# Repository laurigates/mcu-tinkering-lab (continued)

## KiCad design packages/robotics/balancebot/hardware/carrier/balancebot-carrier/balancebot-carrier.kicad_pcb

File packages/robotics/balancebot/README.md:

# Balancebot

Two-wheel self-balancing robot on a **Seeed XIAO RP2350**: an MPU6050 IMU
feeds a 500 Hz complementary filter and either a PID cascade or an LQR
(switchable live) on core 1, and RP2350
PIO state machines generate jitter-free step pulses for two DRV8825-driven
NEMA17 steppers. Tuning happens live over a USB CDC serial CLI; tuned
gains persist to flash.

The repo's first non-ESP32 project — built with the Raspberry Pi Pico SDK
(pinned 2.2.0) inside a container.

Design docs: [PRD-012](../../../docs/requirements/PRD-012-balancebot.md) ·
[ADR-018](../../../docs/decisions/ADR-018-pico-sdk-balancebot.md) ·
[ADR-026](../../../docs/decisions/ADR-026-balancebot-lqr-live-switch.md) ·
[WIRING.md](WIRING.md) ·
[BRINGUP.md](BRINGUP.md) (buck, straps and Vref before the first `arm`)

The project's story, at five levels of technical depth, is on
[GitHub Pages](https://laurigates.github.io/mcu-tinkering-lab/balancebot/)
([source](../../../docs/site/balancebot/index.html)).

A carrier PCB replaces the hand-wired harness: see
[`hardware/carrier/README.md`](hardware/carrier/README.md) for what is on it,
how it is generated from `hardware.toml`, and how to order it.

## Printable build guide

[`docs/build-guide.typ`](docs/build-guide.typ) → [PDF](docs/build-guide.pdf):
the whole build at the bench — bill of materials, wiring reference, power,
assembly, Vref, flashing, first boot and calibration, functional checkout,
tuning, troubleshooting.

Regenerate it after editing — GPIO numbers come from `src/pin_config.h` via
`docs/auto/pin_defs.typ`, so a pin moved in the header changes what it prints:

```bash
just balancebot::build-guide
```

The recipe pins the Typst version and the two determinism flags that
`.github/workflows/build-guide-check.yml` recompiles with, so a hand-run
`typst compile` with different flags will read as drift in CI.

## Build

```bash
# From the repo root (containerized; no local toolchain needed)
just balancebot::build          # → build/balancebot.uf2

# Host-side unit tests (PID, filter, CRC, LQR, param record; no hardware)
just balancebot::test
```

## Flash

```bash
just balancebot::flash          # picotool (reboots the board itself)
just balancebot::flash-uf2      # or: BOOTSEL drag-and-drop instructions
```

A running firmware reboots into BOOTSEL over USB, so the board's buttons are
needed only when it has crashed or its USB never enumerates. Disarm first:

```bash
picotool reboot -u -f                    # BOOTSEL; the RP2350 drive mounts
stty -f /dev/cu.usbmodem<N> 1200         # same, by the 1200-baud request
picotool reboot                          # back to the firmware
```

Both were checked on the robot on 2026-11-24 (fw 0.1.16).

## Tune

```bash
just balancebot::cli "mount down" save   # send commands, print the replies
just balancebot::stat           # also: arm, disarm
just balancebot::monitor        # watch output only; it sends nothing you type
```

```
help                 # command list
stat                 # firmware, state, gains, maxrate, model, calibration, angle, battery, pack, loop time
stream on 50         # CSV telemetry at 50 Hz (plot with any serial plotter)
log                  # run log: on/off, rate, last save, the run stored in flash (see "Untethered run log")
log list             # the runs kept in flash (newest six), newest first
log dump             # print the newest run as CSV (disarmed only); `log dump <n>` prints run n
set kp 30            # live PID gain changes
set l_eff_m 0.14     # LQR model/weight change: re-solves K, prints K, rho, residual
ctrl lqr             # switch to LQR live (bumpless); `ctrl pid` switches back
mount down           # GY-521 fitted component side down (disarmed only); `mount up` is the default
trim capture         # hold still at the balance point 2 s: sets the pitch trim (see "Pitch trim")
arm | disarm         # start/stop balancing (or hold upright 3 s to auto-arm)
drive 0.2            # while balancing: 0.2 m/s forward for 2 s, then ramps to a stop
drive 0.2 0.05 5     # ... plus 0.05 m/s turn (left wheel +, right -; > 0 = clockwise), 5 s
drive 0 0.1          # spin in place; `drive stop` ramps speed and turn to 0
rate l 800           # open-loop motor bench test (disarmed only)
cal                  # gyro bias calibration (keep the robot still); reports ok or moved
save                 # persist gains to flash (survives power cycle)
load                 # reload the saved params, gains and mount from flash (disarmed only)
set pack_r_kohm 22   # carrier divider R3: 27 (delivered boards, the default) or 22 (rev3); then `save`
set pack_cells 4     # cell count the pack warning and cutoff scale with (default 3)
```

`arm`, `mount`, `load`, `rate` and `cal` judge the state after the commands
typed before them have reached core 1 (a pasted `disarm` first is waited for, a
few control ticks at most), and refuse rather than print `OK` when core 1 would ignore them:

- `arm` in FAULT: `ERR: state FAULT — 'disarm' to clear it, or hold upright …`.
  If the IMU is not responding, holding upright cannot clear the FAULT, so the
  refusal offers only `disarm`.
- `arm` that core 1 takes but faults on in the same tick, because the robot
  lies past the 30° tilt cutoff or the IMU does not read:
  `ERR: armed, then FAULT (pitch … deg, tilt cutoff … deg) — …` or
  `ERR: armed, then FAULT — IMU not responding; …` instead of `OK`.
- `mount` and `load` while armed: `ERR: disarm first …`. Core 1 keeps the
  mount while armed. If the hold-upright gesture arms it before a `mount` (or
  the mount in `load`) arrives, the CLI says the mount stays where it was and
  `get` shows the mount core 1 applies. `load` says whether a stored record
  was found either way; when the mount was not confirmed, the parameters,
  gains and controller were still applied.
- `rate` and `cal` outside IDLE: `ERR: state RUN — 'disarm' first; …`. Core 1
  runs them only disarmed.
- Any of them while core 1 is still busy with earlier commands (a `save`
  stalls it ~45 ms): `ERR: core 1 busy …`; nothing is sent, so repeat it.

CSV columns: `t_ms,state,angle_deg,gyro_dps,setpoint_deg,rate_sps,loop_us,ctrl,pos_m,pack_v`
(`ctrl` 0 = PID, 1 = LQR; `pos_m` = commanded wheel travel since arming;
`pack_v` = pack voltage in volts, `nan` with no pack on D0).
Columns are only ever appended, so plots that index by position keep working.

### Fitting `l_eff_m` from a capture

```bash
just balancebot::capture 20                         # 20 s at 100 Hz -> tmp/balancebot/capture-<time>.csv
just balancebot::fit-leff tmp/balancebot/capture-<time>.csv 0.065   # path from the repo root; wheel diameter in m
```

Arm the robot, let it balance on its own for the capture, and do not push it:
a push is a force the LQR model lacks and drags the fit. `fit-leff` fits the
model in `src/lqr.h` to the RUN rows and prints `l_eff_m` with a 1-sigma
range, R², and the angle the balance point reads (what to add to `trim`).
Stretches where a motor stalled or skipped steps break the fit too, since the
wheel speed in the CSV is the commanded one; with R² under 0.3 it says not to
trust the result. On simulated captures it is within about 11 % (1 sigma);
`tools/fit_leff.py --self-test` runs in the host test suite.

**On the rev1 robot it has not worked.** Three balancing captures on
2026-11-23 gave R² 0.13, 0.06 and below 0.3, with `l_eff_m` estimates of
0.41 and 0.97 m that the robot's geometry rules out. A well-tuned robot moves
too little to fit, and a badly tuned one spends its time at the acceleration
clamp. Its offset estimate did agree with the mean angle, which `analyze`
reports directly. Estimate `l_eff_m` from the geometry instead ("Tuning
loop"); the LQR tolerated a rough value there.

### IMU mounting

The filter expects the GY-521 component side up, X arrow forward. On the
8d18cd8d carrier (the boards from the 2026-10-23 order) the module only wires
correctly fitted component side down, hanging rearward: that turns it 180°
about the axle, so accel X and Z both read inverted while gyro Y does not.
`IMU_PITCH_SIGN` cannot correct that (a level board reads about 180°), so the
mounting is a setting:

```
mount down           # negate accel X and Z before the filter
save                 # stored in the flash record (PARAM_VERSION 3 and later)
```

Change it only while disarmed; `stat` shows the mounting core 1 applies. With
the right setting a level board reads about 0° and tilting forward reads
positive. Records saved by older firmware load as `mount up`.

### Status LEDs

The yellow user LED blinks slowly in IDLE, stays on in RUN and blinks fast
in FAULT. The XIAO's RGB LED helps you find the auto-arm window by eye. It
uses the trimmed angle, the same one the gesture uses:

| RGB | Meaning |
|---|---|
| dim blue | IDLE, more than 5° from upright |
| yellow | within 5°: getting close |
| green, brightening | inside the ±3° window; full brightness when the 3 s hold arms it |
| solid green | RUN |
| purple | auto-arm held off (after `disarm` or `trim capture`) |
| red, blinking | FAULT |
| red, solid | IMU not responding |
| cyan, pulsing | core 1 starting (IMU init, gyro calibration) |

Brightness is capped at about 16 % of full scale.

### Pitch trim

A module that sits a degree or two off parallel to the carrier, or a robot
whose centre of mass is not over the axle when the carrier is level, balances
at a pitch other than 0. The controllers, the 3 s auto-arm window (±3°) and
the tilt cutoff all work from 0, so the robot then drives to correct a lean
that is not there, and may never auto-arm. `trim` moves 0 to the balance point:

1. Disarmed, hold the robot still where it balances and run `trim capture`
   (`just balancebot::cli "trim capture" save`).
2. For 2 s it averages the pitch; the trim becomes the current trim plus that
   average, so running it again only corrects what is left.

It refuses, leaving the trim unchanged, when the robot moved during the 2 s,
when the result would pass ±10° (usually a wrong `mount`), or when the
hold-upright gesture arms the robot first (the pose already read within ±3°
for 3 s). `set trim <deg>` sets it by hand. `trim` is subtracted from every
pitch sample, so telemetry shows the trimmed angle. It is limited to ±10° and
can be changed while armed. Records saved before PARAM_VERSION 4 load with
`trim 0`.

### Gyro calibration

The gyro bias is measured at boot, over 1 s with the robot at rest. If the
gyro or accel spreads more than a still robot would in that second (3 °/s
or 0.1 g peak to peak), the window is discarded and repeated, up to five
times; after that the robot runs with the last good bias, or none. `stat`
shows the result on its `gyro cal:` line, and `cal` repeats it on demand,
reporting `OK` or that the robot moved.

### A held I2C bus

A reset in the middle of an IMU read can leave the MPU6050 holding SDA low,
and USB power keeps it in that state across a reboot. Older firmware then
hung core 1 before its loop, and `stat` showed `imu: NOT RESPONDING` with
tick 0. Now every I2C transfer is bounded to 1 ms, and a held line is
freed (up to nine SCL clocks, then a STOP) at init and after any timed-out
transfer. `stat` counts these on an `imu bus:` line. During the first few
seconds after boot (IMU init and the gyro calibration) `stat` opens with
`core 1: starting`, and its readings are not live yet. If core 1 is still in
startup 10 s after boot, it says `core 1: STUCK in startup`; power-cycle the
robot with USB and battery both disconnected.

`arm` is refused while the robot rests with the mounted Z axis reading below
-0.5 g (more than 120° from upright), because at rest that means the setting
does not match the board:
`ERR: IMU reads upside down (body Z = -0.98 g); check 'mount' (now up)`. Stand
the robot upright; if it still refuses, switch `mount` and `save`. "At rest"
means the accelerometer reads 1 g ± 0.15 g and the gyro under 10 °/s
(`IMU_STILL_*` in `src/imu_filter.h`); a moving sample is not refused by this
check, and the tilt cutoff still applies. `arm` checks the mount core 1
applies: a `mount` typed just before it (a paste, a script) is waited for, a
few control ticks at most. Core 1 checks again when it handles the arm; if it
refuses, `arm` prints `ERR: core 1 refused arm: …` instead of `OK`, and `stat`
counts the refusals.

### Tuning procedure (PID)

The default `kp` (28) is far below the roughly 970–1340 (steps/s²)/° it takes
to catch a fall with 90–65 mm wheels (#742), and the rev1 robot was tuned on
the LQR instead ("Tuning loop" below). The PID procedure, untested on the
robot:

1. Bench-check: `rate l 800` / `rate r 800` — both wheels spin smoothly,
   `rate l 0` stops. `stream on`, tilt the frame — angle tracks.
2. Set `ki`/`vkp`/`vki` to 0. Raise `kp` until the robot visibly fights
   the fall (fast oscillation = too high).
3. Raise `kd` to damp the oscillation.
4. Restore small `vkp`/`vki` so it holds station instead of wandering.
5. `save`.

### LQR

The LQR ([ADR-026](../../../docs/decisions/ADR-026-balancebot-lqr-live-switch.md))
uses a wheeled-inverted-pendulum model whose input is the same wheel
acceleration the PID commands. Core 0 solves the gains in double precision at
boot and whenever one of its parameters changes. Core 1 only applies them.

| Param | Meaning | Default |
|-------|---------|---------|
| `l_eff_m` | Equivalent pendulum length (m) | 0.12 (placeholder) |
| `wheel_diam_m` | Wheel diameter (m) | 0.09 (placeholder) |
| `steps_per_rev` | Microsteps per wheel revolution | 1600 |
| `q_theta` `q_dtheta` `q_x` `q_dx` | State weights | 400, 1, 25, 4 |
| `r` | Input weight | 0.04 |

Every model or weight change re-solves K and prints K, the closed-loop
spectral radius `rho` (it must be below 1) and the residual. A change whose
solve fails is rejected and leaves both the parameter and K unchanged. The
LQR settings, `alpha` and `trim` can all change while armed: core 1 takes the
new gains on the next tick, as a step (unlike the bumpless `ctrl` switch).
Only `save` needs the robot disarmed. `ctrl pid` switches back to the PID;
that switch is bumpless only with `ki` ≠ 0. `save` stores the mode and the
model; K is re-solved at boot, and if that solve fails the robot runs the
PID and says so.

### Tuning loop

How the rev1 robot went from falling over in 15 s to holding its spot within
about 1 cm on 2026-11-23:

1. **Signs** ([`BRINGUP.md`](BRINGUP.md) §4), then the model:
   `set wheel_diam_m` to the measured wheel and `set l_eff_m` to an
   estimate. For a body of even mass pivoting on the axle that is ⅔ of its
   height; with the battery on top it is close to the axle-to-battery
   distance (0.21 m for the rev1 robot's 24 cm with three 18650s on top).
   The swing test (hang it by the axle and time small swings,
   `L_eff = 9.81 · (T / 2π)²`) needs hands for both the robot and a stopwatch,
   and the robot's swing damps out after one or two cycles.
2. `ctrl lqr`, `save`, and arm it upright **on the floor**.
3. Loop: `just balancebot::capture 20` while it balances on its own, then
   `just balancebot::analyze <csv>`, then change one setting live, then
   capture again. `analyze` names the next change:

   | `analyze` shows | Cause | Change |
   |---|---|---|
   | a large share at the acceleration clamp, jitter | gains ask more than the motors may give | raise `r` ("Choosing r") |
   | a rock near the pendulum frequency √(g/L) | the accelerometer reads the robot's own acceleration as tilt | raise `alpha` (0.996 at 500 Hz) |
   | position held, mean angle away from 0 | trim | add the mean to `trim` |
   | position wandering | position hold too weak | raise `q_x` / `q_dx`, or lower `r` |

4. `just balancebot::cli disarm save` once it holds.

The rev1 run, each line one 20 s capture:

| Settings | angle RMS | at clamp | peak speed | position range |
|---|---|---|---|---|
| r 0.04, alpha 0.98 | 3.69° | 48 % | 4000 (limit) | 39 cm |
| r 10, alpha 0.98 | 1.40° | 0 % | 1164 steps/s | 4.5 cm |
| r 10, alpha 0.996 | 0.23° | 0 % | 470 steps/s | 2.0 cm |
| + trim −5.47° | 0.25° | 0 % | — | 1.2 cm (10 s) |

### Untethered run log

The robot records every run without the cable (ADR-037,
[`docs/decisions/ADR-037-balancebot-untethered-run-log.md`](../../../docs/decisions/ADR-037-balancebot-untethered-run-log.md)).
From the moment it arms until 1 s after it falls or is disarmed, core 0 samples
the same columns as `stream` into RAM, at 100 Hz by default (`log on 200` for
200 Hz, `log off` to stop). When the run ends it copies it to flash, which takes
about 0.06 s per 1.3 s of run. The CLI and LED pause meanwhile, and the auto-arm
gesture is held off until it is done. RAM holds the last 82 s at 100 Hz (41 s at
200 Hz). A longer run keeps its end, including the fall. Flash keeps the newest six
runs; `log list` shows them with their run numbers.

1. With USB and the pack connected (USB first, #1230), check `log` says `on`,
   then unplug USB.
2. Arm it on the floor and push, drive or let it fall.
3. Leave it lying for a second, then disconnect the pack.
4. Plug in USB (the XIAO runs from USB alone) and read the run:

   ```bash
   just balancebot::log-dump                     # newest run -> tmp/balancebot/log-<time>.csv
   just balancebot::log-dump n=12                # run 12 from `log list`
   just balancebot::analyze tmp/balancebot/log-<time>.csv
   ```

`log` shows whether the last save worked. A run is not saved if the robot is
re-armed within the 1 s tail, or if power drops before a FAULT or disarm is
seen (a brownout or the pack's BMS cutting out).

### Choosing r

`just balancebot::lqr-sweep <l_eff_m> <wheel_diam_m> [r...]` prints K, the
closed-loop poles and the lean at which K's angle gain alone reaches the
acceleration clamp, for each r. For the rev1 model (0.21 m, 65 mm wheels):

| r | K | clamp at | |
|---|---|---|---|
| 0.04 (default) | −134, −14.5, −23.9, −26.4 | 2.2° | jitters against the clamp |
| 10 | −27.0, −3.9, −1.56, −2.42 | 10.8° | the rev1 setting |
| 50 | −23.6, −3.4, −0.70, −1.43 | 12.4° | |

Raising r makes the robot gentler until about 10–50. Past that the angle
poles stop at the mirror of the robot's own falling pole −√(g/L), and only the
position hold keeps weakening, so the robot drifts more after a push for no
extra smoothness. The 0.04 default suits the placeholder model, not 65 mm
wheels and the 40 000 steps/s² clamp.

## Safety model

- DRV8825 nENABLE has an external 10 kΩ pull-up: drivers are **disabled**
  while the MCU boots, resets, or sits in BOOTSEL.
- Tilt cutoff: |pitch| > 30° disables the drivers (FAULT, fast LED blink);
  clears after 2 s upright.
- Low-pack cutoff (carrier PCB only): core 0 reads the pack through the divider
  on D0 (`stat` line `pack:`) ten times a second. Below 3.5 V per cell (10.5 V
  for 3S) it warns; below 3.0 V per cell (9.0 V for 3S) for 1 s it latches, and
  core 1 stops the motors with a FAULT, the same as the tilt cutoff, and
  refuses `arm` and the auto-arm gesture. The latch releases once the pack
  reads 0.3 V per cell above the cutoff (9.9 V for 3S). The FAULT also saves
  the run log (ADR-037). Set `pack_r_kohm` to the board's R3 (27 for the
  delivered boards, 22 for rev3) and `pack_cells` to the pack; a wrong
  `pack_r_kohm` reads about 18 % off. With nothing on D0 (the hand-wired
  harness) `stat` says `pack: absent`, the CSV column `pack_v` is `nan`, and
  nothing is stopped. The BMS cutoff stays the backup (ADR-038).
- Hardware watchdog (100 ms) fed only by the control loop, enabled at
  first arm — a wedged loop reboots into motors-off.
- Motors arm only via `arm` or the deliberate hold-upright-3 s gesture.

## Architecture

| Where | What |
|-------|------|
| Core 1 | 500 Hz loop: IMU burst read → complementary filter → angle PID or LQR (output = wheel **acceleration**) → integrate to step rate → PIO periods. Tilt cutoff, watchdog, flash saves. |
| Core 0 | USB CDC CLI, CSV telemetry, status LED, battery ADC, LQR gain solve. |
| PIO0 SM0/SM1 | STEP pulse trains, 30–20 000 steps/s, cycle-accurate, hold-last-rate between updates. |

Core 0 → core 1: lock-free command queue. Core 1 → core 0: seqlock
snapshot. The control loop never blocks and never prints.

`src/pin_config.h` is the pin-map source of truth; see
[WIRING.md](WIRING.md) for the full harness.

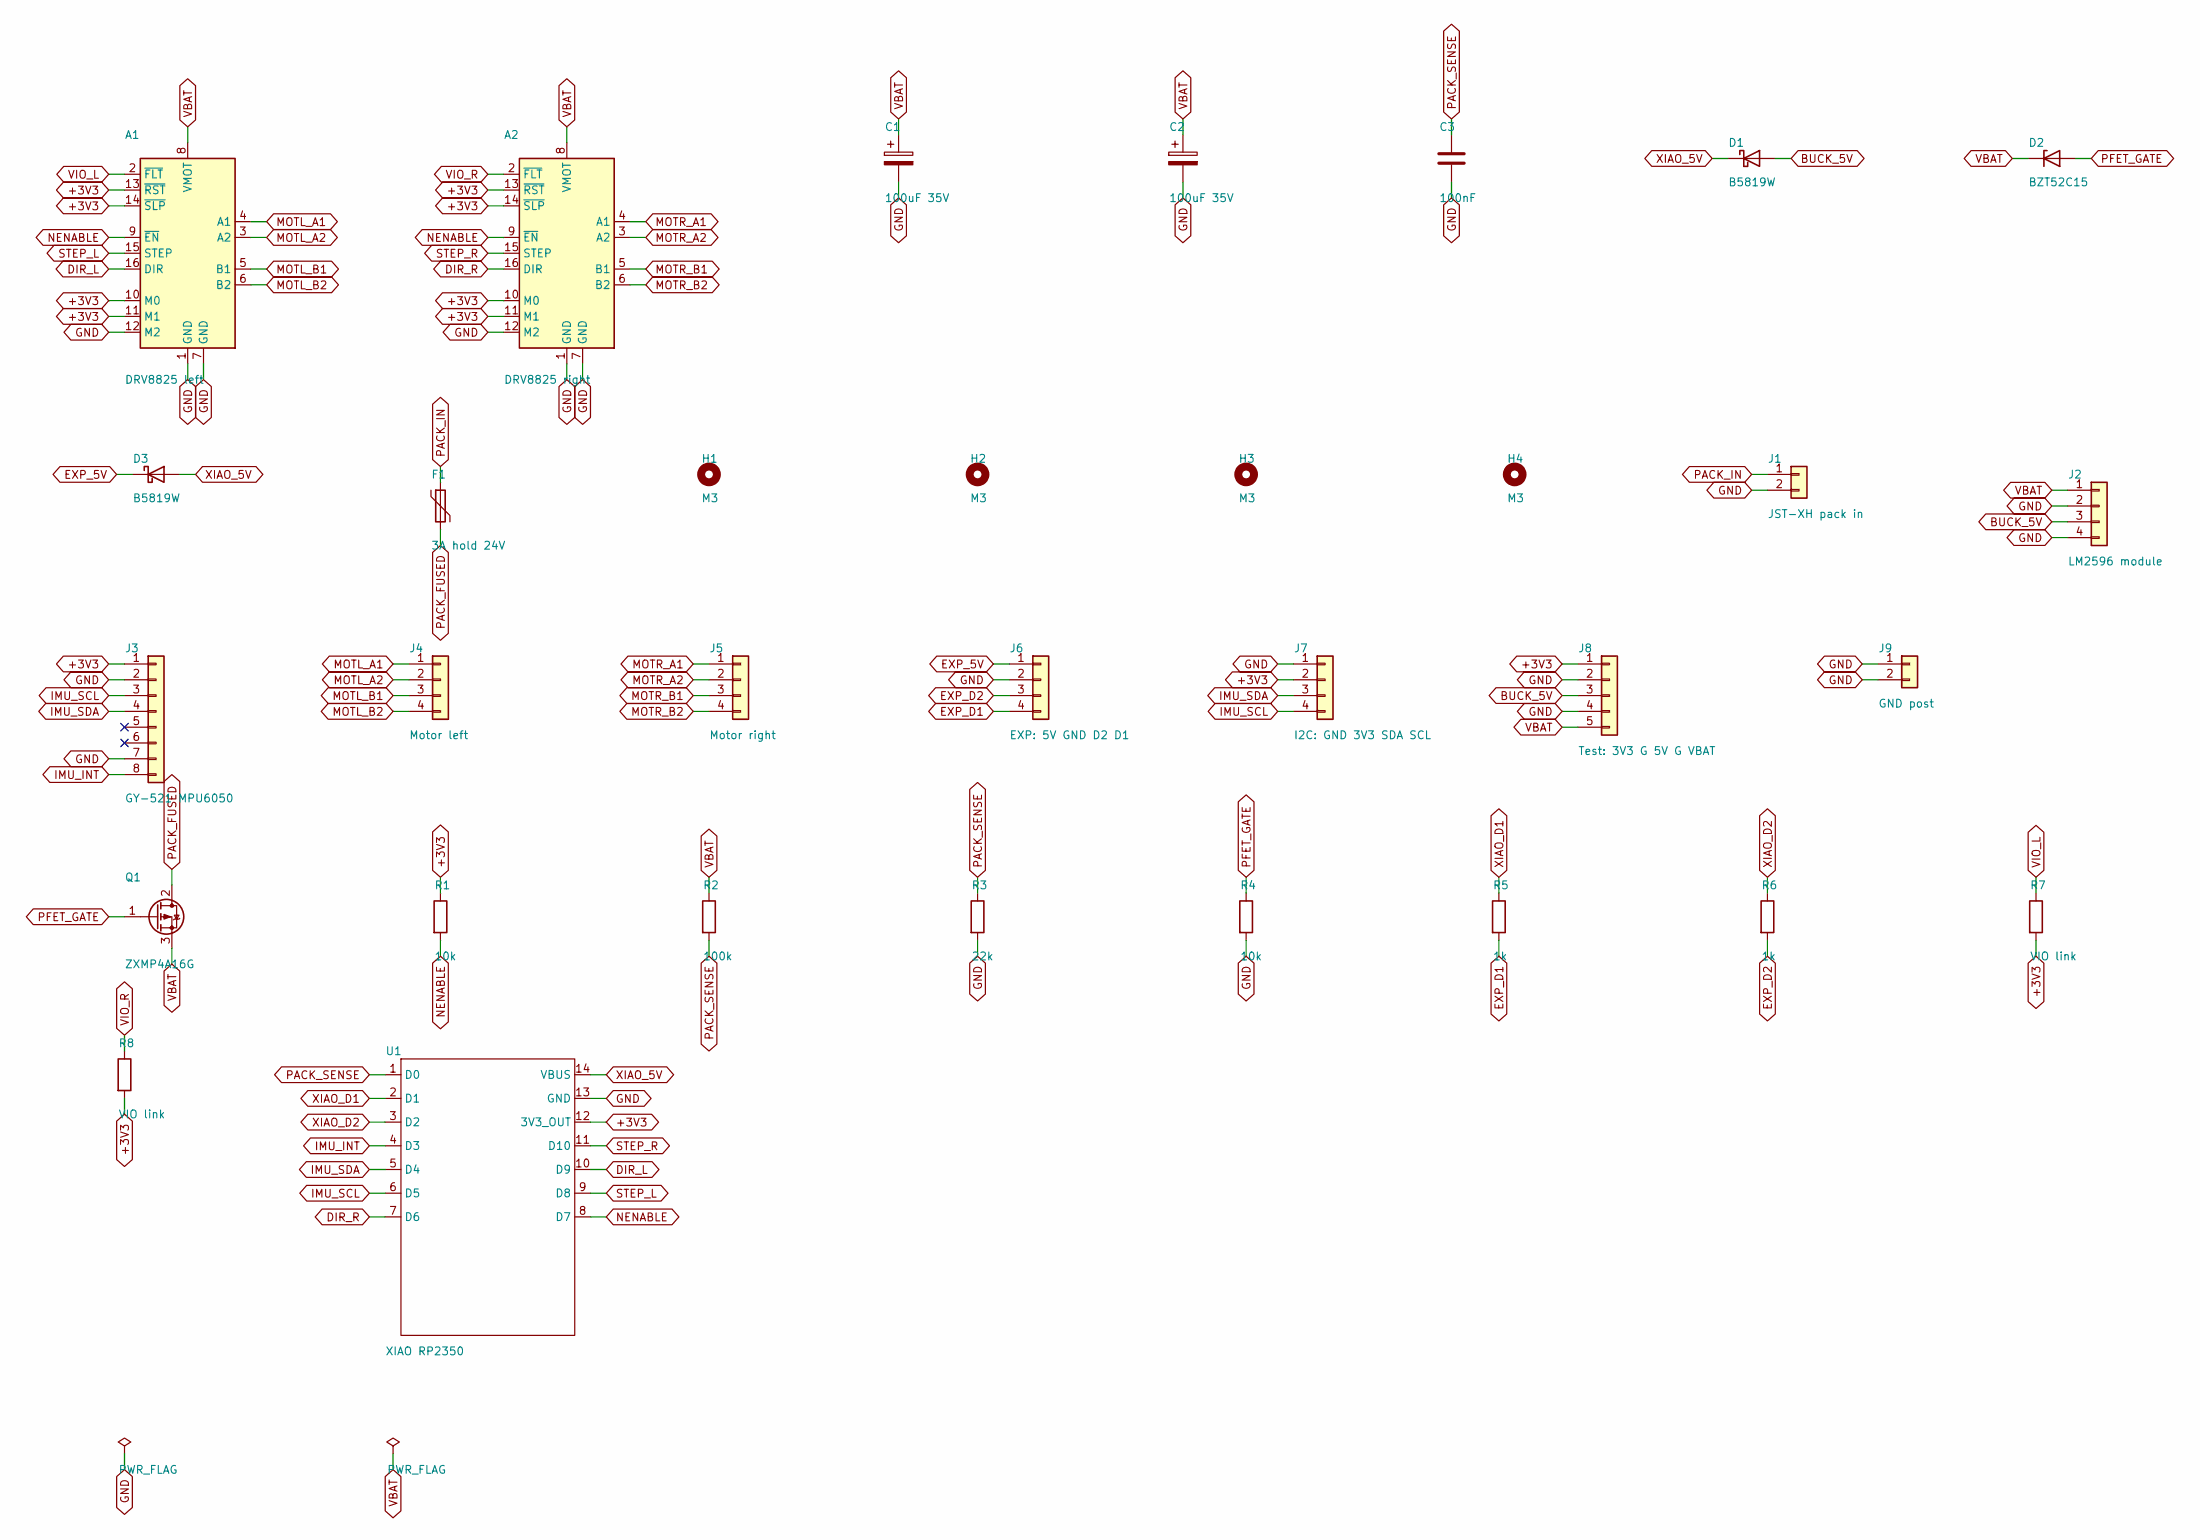
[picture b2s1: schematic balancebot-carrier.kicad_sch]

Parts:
A1: DRV8825 left; Pololu_Breakout-16_15.2x20.3mm
A2: DRV8825 right; Pololu_Breakout-16_15.2x20.3mm
C1, C2: 100uF 35V; CP_Elec_6.3x7.7; LCSC C2836437
C3: 100nF; C_0805_2012Metric_Pad1.18x1.45mm_HandSolder; LCSC C49678
D1, D3: B5819W; D_SOD-123; LCSC C8598
D2: BZT52C15; D_SOD-123; LCSC C2104
F1: 3A hold 24V; Fuse_1812_4532Metric_Pad1.30x3.40mm_HandSolder; LCSC C7500481
H1, H2, H3, H4: M3; MountingHole_3.2mm_M3
J1: JST-XH pack in; JST_XH_B2B-XH-A_1x02_P2.50mm_Vertical
J2: LM2596 module; JST_XH_B4B-XH-A_1x04_P2.50mm_Vertical
J3: GY-521 MPU6050; GY521_Socket
J4: Motor left; JST_XH_B4B-XH-A_1x04_P2.50mm_Vertical
J5: Motor right; JST_XH_B4B-XH-A_1x04_P2.50mm_Vertical
J6: EXP: 5V GND D2 D1; PinHeader_1x04_P2.54mm_Vertical
J7: I2C: GND 3V3 SDA SCL; PinHeader_1x04_P2.54mm_Vertical
J8: Test: 3V3 G 5V G VBAT; PinHeader_1x05_P2.54mm_Vertical
J9: GND post; PinHeader_1x02_P2.54mm_Vertical
Q1: ZXMP4A16G; SOT-223-3_TabPin2; LCSC C141324
R1, R4: 10k; R_0805_2012Metric_Pad1.20x1.40mm_HandSolder; LCSC C17414
R2: 100k; R_0805_2012Metric_Pad1.20x1.40mm_HandSolder; LCSC C149504
R3: 22k; R_0805_2012Metric_Pad1.20x1.40mm_HandSolder; LCSC C17560
R5, R6: 1k; R_0805_2012Metric_Pad1.20x1.40mm_HandSolder; LCSC C17513
R7, R8: VIO link; R_0805_2012Metric_Pad1.20x1.40mm_HandSolder
U1: XIAO RP2350; XIAO-RP2350-Socket

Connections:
+3V3: A1.10 (M0), A1.11 (M1), A1.13 (~RST), A1.14 (~SLP), A2.10 (M0), A2.11 (M1), A2.13 (~RST), A2.14 (~SLP), J3.1, J7.2, J8.1, R1.1, R7.2, R8.2, U1.12 (3V3_OUT)
BUCK_5V: D1.2 (A), J2.3, J8.3
DIR_L: A1.16 (DIR), U1.10 (D9)
DIR_R: A2.16 (DIR), U1.7 (D6)
EXP_5V: D3.1 (K), J6.1
EXP_D1: J6.4, R5.2
EXP_D2: J6.3, R6.2
GND: A1.1 (GND), A1.7 (GND), A1.12 (M2), A2.1 (GND), A2.7 (GND), A2.12 (M2), C1.2, C2.2, C3.2, J1.2, J2.2, J2.4, J3.2, J3.7, J6.2, J7.1, J8.2, J8.4, J9.1, J9.2, R3.2, R4.2, U1.13 (GND)
IMU_INT: J3.8, U1.4 (D3)
IMU_SCL: J3.3, J7.4, U1.6 (D5)
IMU_SDA: J3.4, J7.3, U1.5 (D4)
MOTL_A1: A1.4 (A1), J4.1
MOTL_A2: A1.3 (A2), J4.2
MOTL_B1: A1.5 (B1), J4.3
MOTL_B2: A1.6 (B2), J4.4
MOTR_A1: A2.4 (A1), J5.1
MOTR_A2: A2.3 (A2), J5.2
MOTR_B1: A2.5 (B1), J5.3
MOTR_B2: A2.6 (B2), J5.4
NENABLE: A1.9 (~EN), A2.9 (~EN), R1.2, U1.8 (D7)
PACK_FUSED: F1.2, Q1.2 (D)
PACK_IN: F1.1, J1.1
PACK_SENSE: C3.1, R2.2, R3.1, U1.1 (D0)
PFET_GATE: D2.2 (A), Q1.1 (G), R4.1
STEP_L: A1.15 (STEP), U1.9 (D8)
STEP_R: A2.15 (STEP), U1.11 (D10)
VBAT: A1.8 (VMOT), A2.8 (VMOT), C1.1, C2.1, D2.1 (K), J2.1, J8.5, Q1.3 (S), R2.1
VIO_L: A1.2 (~FLT), R7.1
VIO_R: A2.2 (~FLT), R8.1
XIAO_5V: D1.1 (K), D3.2 (A), U1.14 (VBUS)
XIAO_D1: R5.1, U1.2 (D1)
XIAO_D2: R6.1, U1.3 (D2)

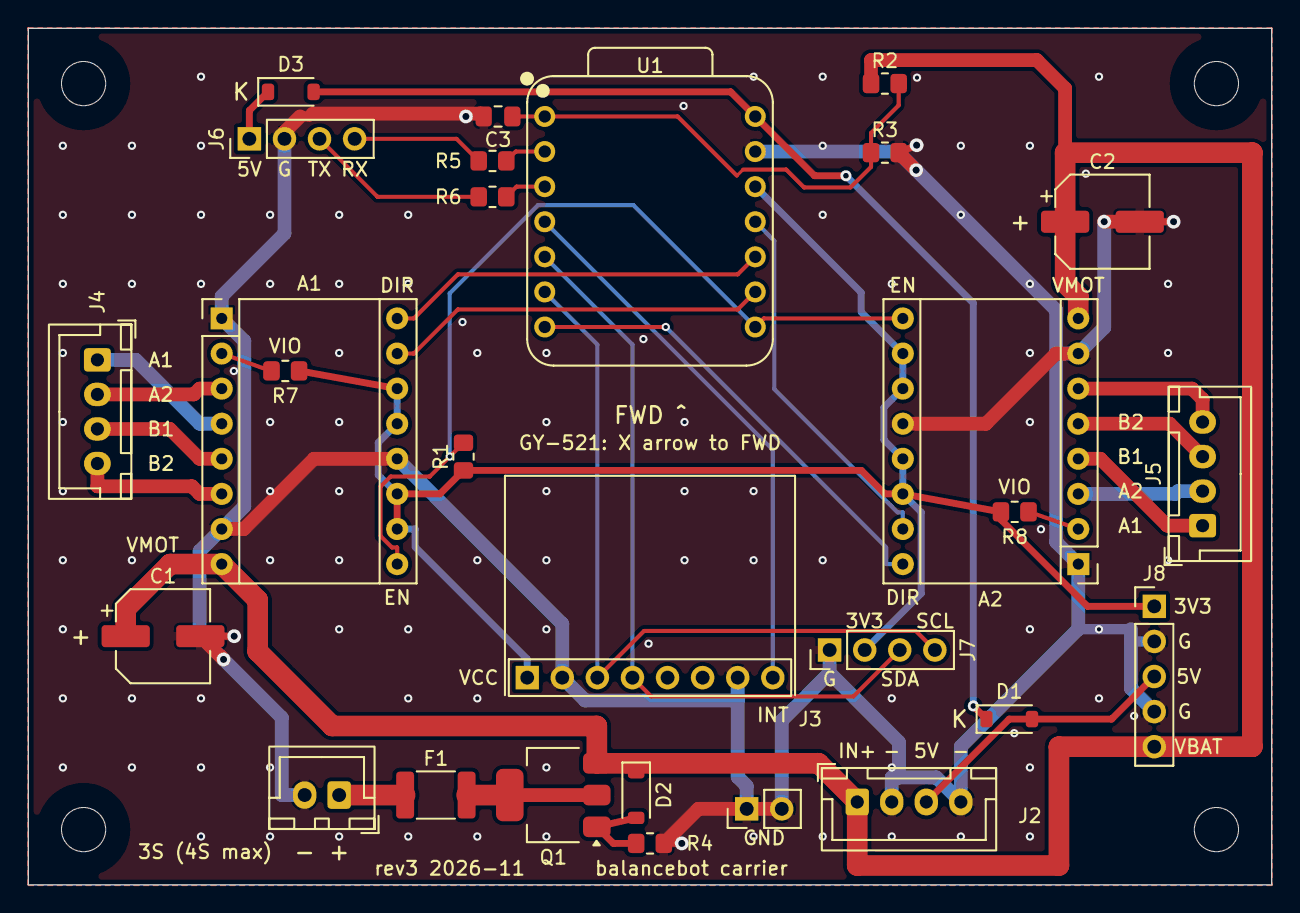
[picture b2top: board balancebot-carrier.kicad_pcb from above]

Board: 2 copper layers, 90.0 x 62.0 mm, 32 parts (0 on the bottom side), 32 nets.

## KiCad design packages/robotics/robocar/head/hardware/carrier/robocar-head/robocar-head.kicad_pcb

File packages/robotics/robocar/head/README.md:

# robocar head panel PCB

The three head boards that carry the XIAO ESP32-S3 Sense in the pan-tilt kit's
top cradle: one 29.5 × 100 mm, 2-layer PCB, sawn into three 29.5 × 29.5 mm
heads after delivery. Each head is a XIAO socket and the head end of the 2 × 8
ribbon; they differ only in where the ribbon header sits. Fit the XIAO to the
one that suits the cradle.

The heads were a column on the right of the
[main board's panel](../hardware/carrier/README.md) until #1280 (Lauri,
2026-11-25), when the main board needed their area for the power switch, soft
latch and USB charger (ADR-038). The layout is that column's, moved 70.5 mm
left: x = 0 here was x = 70.5 there.

This directory holds no firmware and no `hardware.toml` of its own. The KiCad
project, [`hardware/carrier/robocar-head/`](hardware/carrier/robocar-head/), is
the head side of the parent's [`hardware.toml`](../hardware.toml): its
[`board.toml`](hardware/carrier/board.toml) says `[project] side = "head"` and
`join = ".."`, and `tools/kicad/netlist.py` keeps the XIAO sockets (U1, U3,
U4), the ribbon headers (J2, J16, J17) and the cable's `head_parts`, the M2
holes (H5–H10). Never edit the `.kicad_sch` or `.kicad_pcb` in KiCad.

## The three heads

All three have the same outline, the same two M2 holes in the top corners
(22.5 mm apart, the positions Lauri confirmed on 2026-10-16), and the XIAO with
its USB-C toward the top edge, which points the Sense camera forward. The
cradle's sides carry clips, so the header sits at the top or the bottom edge,
never at a side (Lauri, 2026-10-16). Only one head gets a XIAO; the other two
stay spare.

| Head | Refs | Header | XIAO | For |
|---|---|---|---|---|
| 1 | U1, J2, H5, H6 | Back face, bottom edge | Between the holes, above the header | The plug and ribbon behind the head, leaving the bottom edge |
| 2 | U3, J16, H7, H8 | Front face, bottom edge | Between the holes, above the header | The plug in front, below the camera, if nothing behind the head clears it |
| 3 | U4, J17, H9, H10 | Back face, top edge, between the holes | Below the holes | The ribbon leaving over the top, if the bottom edge is blocked |

The holes use KiCad's ISO 7380 M2 footprint, whose courtyard is a 3.5 mm button
head: on heads 1 and 2 the XIAO socket sits 0.26 mm from it on each side. Fit
M2 button-head screws (ISO 7380) or another head no larger than 3.5 mm.

Each head's copy of the XIAO socket is wired to its own header (nets `HEAD_*`,
`HEAD2_*`, `HEAD3_*`). The main board has a single end, J1, so moving the
ribbon to another head moves the robot to it. The ribbon's pinout and why a
reversed plug is harmless are in the main board's
[README](../hardware/carrier/README.md#the-ribbon-survives-a-reversed-plug).

## Layout changes since the shared panel (#1280)

- **The left edge is milled now, not sawn**, so copper comes to 0.5 mm of it,
  1 mm closer than beside the old vertical cut.
- **The 2 × 8 headers** (ADR-038) are 2 mm longer than the 2 × 7 ones, at the
  same pin 1. J16 sits 1 mm left of its old position.
- **Signal tracks are 0.2 mm.** The headers' 1.35 mm pads at 2.0 mm pitch
  leave 0.65 mm between pins: a 0.2 mm track passes there with 0.2 mm
  clearance each side, a 0.3 mm one does not. At 0.3 mm head 2 left one or two
  signals unrouted in 25 attempts. The heads' signals are I2C, I2S, UART0 and
  slow control lines.

## Pre-order checks (Lauri)

1. **The header behind or in front of the head.** For each head you mean to
   use, check the IDC plug and the ribbon's bend clear the cradle and the pan
   servo. On head 2 (header on the front) also fit the XIAO in its socket and
   push the plug onto J16: the plug is wider than the header and stands about
   as tall as the socketed XIAO, so it may touch the XIAO or only leave toward
   the bottom edge. This can wait for the plugs: heads 1 and 3 do not depend
   on it.
2. **Saw kerf against the bands.** A blade wider than about 1 mm leaves no bare
   margin beside the cut line in a 3 mm band.

## Separating the heads

Every cut is straight across the panel, so no cut ends in an inside corner and
none needs a relief hole.

1. **Buy a jeweller's saw frame with fine blades** (or a coping saw with a fine
   blade).
2. **Clamp the panel** flat, the cut line just past the bench edge.
3. **Cut the panel into its three heads** along the four horizontal lines. Each
   head's lines are its own edges; keep the kerf in the waste strips between
   heads (y 29.5–35.25 and 64.75–70.5), where the "CUT" labels are.
4. **Sand each head back to its lines, 29.5 × 29.5 mm,** on sandpaper on a flat
   surface, checking with calipers. The cradle's inner size is 30.0 × 30.0 mm.

The closest copper to any cut is a HEAD3_XIAO_5V track, 0.91 mm inside head
3's top edge (the y 70.5 line; `carrier-review`, 2026-11-26). That is above the
board's 0.5 mm copper-to-edge clearance, but leaves no room for a kerf on the
line: saw in the waste strip above it and sand down to the line.

FR-4 dust contains glass fibre: wet-sand, and wear a mask. The heat-set
inserts go in the cradle, not the PCB: H5–H10 are plain 2.2 mm clearance holes.

## Regenerate and check

```sh
just robocar-head::carrier-schematic  # schematic + library tables (no KiCad)
just robocar-head::carrier-board      # place from scratch, autoroute, pour
just robocar-head::carrier-check      # ERC, DRC + parity, netlist parity, board check, stamp
just robocar-head::carrier-fab        # carrier-check, then Gerbers and drill files
```

A change to the parent's `hardware.toml` regenerates both this project and the
main board's; run both checks.

## Ordering

1. **Generate the files** with `just robocar-head::carrier-fab` from a clean
   tree. The panel has no SMD parts, so there is no assembly BOM to use.
2. **Upload the zip** at jlcpcb.com: 2 layers, 29.5 × 100 mm, FR-4, 1.6 mm,
   1 oz, HASL. The order selects high-precision silkscreen (the 0.8 mm
   HEAD 3 label); `carrier-fab` prints the reminder. In the Gerber preview
   check the four "CUT" lines and J2's and J17's outlines on the bottom
   silkscreen.
3. **Buy the parts** for the one head fitted:

   | Qty | Part |
   |---|---|
   | 2 | 1×7 female header, 2.54 mm (the XIAO's socket) |
   | 1 | 2×8 pin header, 2.0 mm pitch (J2, J16 or J17) |
   | 2 | M2 button-head screws, ISO 7380 (or any head of 3.5 mm diameter or less), and 2 M2 heat-set inserts (cradle) |

   The ribbon and its plugs are on the main board's list.

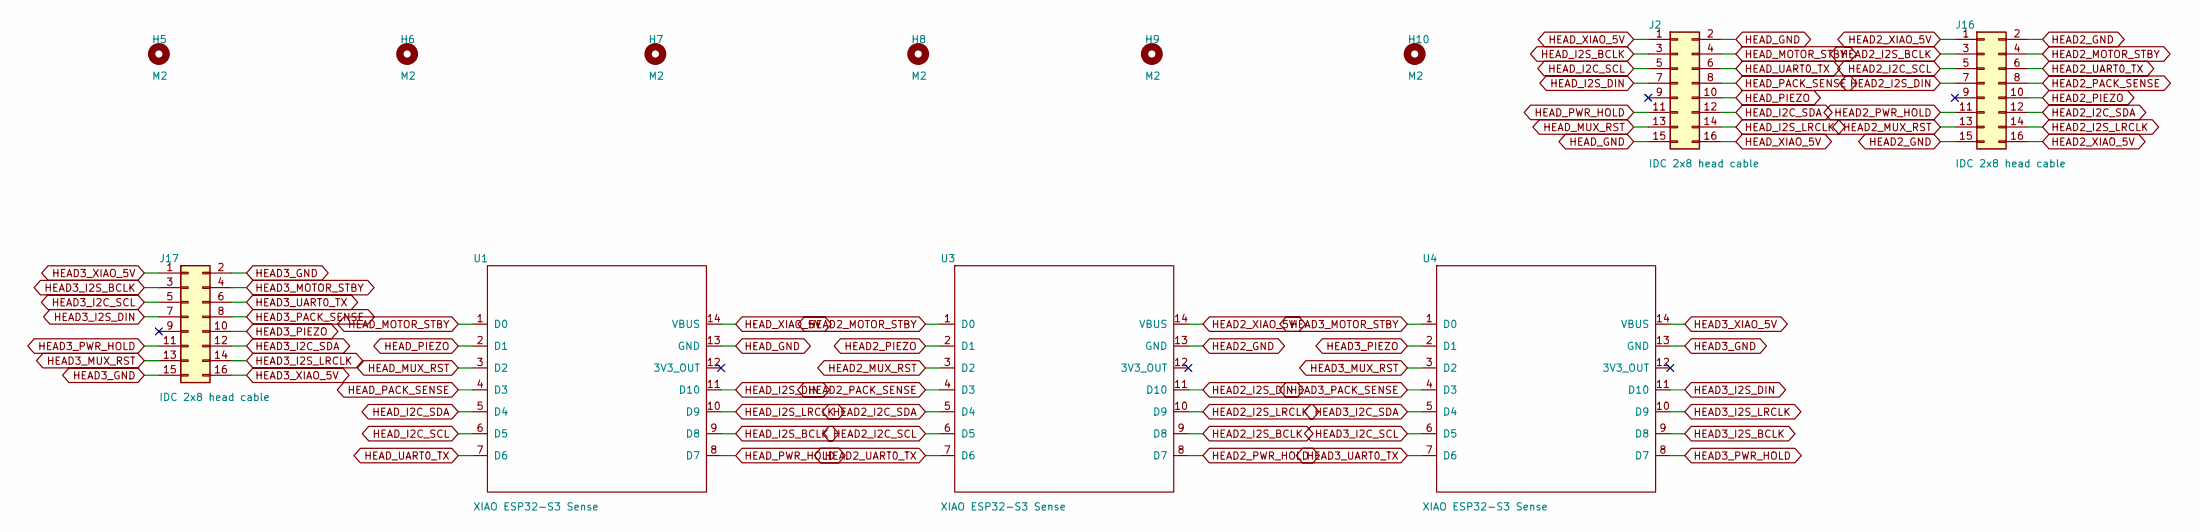
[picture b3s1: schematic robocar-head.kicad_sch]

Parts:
H5, H6, H7, H8, H9, H10: M2; MountingHole_2.2mm_M2_ISO7380
J2, J16, J17: IDC 2x8 head cable; PinHeader_2x08_P2.00mm_Vertical
U1, U3, U4: XIAO ESP32-S3 Sense; XIAO-ESP32-S3-Socket

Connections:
HEAD2_GND: J16.2, J16.15, U3.13 (GND)
HEAD2_I2C_SCL: J16.5, U3.6 (D5)
HEAD2_I2C_SDA: J16.12, U3.5 (D4)
HEAD2_I2S_BCLK: J16.3, U3.9 (D8)
HEAD2_I2S_DIN: J16.7, U3.11 (D10)
HEAD2_I2S_LRCLK: J16.14, U3.10 (D9)
HEAD2_MOTOR_STBY: J16.4, U3.1 (D0)
HEAD2_MUX_RST: J16.13, U3.3 (D2)
HEAD2_PACK_SENSE: J16.8, U3.4 (D3)
HEAD2_PIEZO: J16.10, U3.2 (D1)
HEAD2_PWR_HOLD: J16.11, U3.8 (D7)
HEAD2_UART0_TX: J16.6, U3.7 (D6)
HEAD2_XIAO_5V: J16.1, J16.16, U3.14 (VBUS)
HEAD3_GND: J17.2, J17.15, U4.13 (GND)
HEAD3_I2C_SCL: J17.5, U4.6 (D5)
HEAD3_I2C_SDA: J17.12, U4.5 (D4)
HEAD3_I2S_BCLK: J17.3, U4.9 (D8)
HEAD3_I2S_DIN: J17.7, U4.11 (D10)
HEAD3_I2S_LRCLK: J17.14, U4.10 (D9)
HEAD3_MOTOR_STBY: J17.4, U4.1 (D0)
HEAD3_MUX_RST: J17.13, U4.3 (D2)
HEAD3_PACK_SENSE: J17.8, U4.4 (D3)
HEAD3_PIEZO: J17.10, U4.2 (D1)
HEAD3_PWR_HOLD: J17.11, U4.8 (D7)
HEAD3_UART0_TX: J17.6, U4.7 (D6)
HEAD3_XIAO_5V: J17.1, J17.16, U4.14 (VBUS)
HEAD_GND: J2.2, J2.15, U1.13 (GND)
HEAD_I2C_SCL: J2.5, U1.6 (D5)
HEAD_I2C_SDA: J2.12, U1.5 (D4)
HEAD_I2S_BCLK: J2.3, U1.9 (D8)
HEAD_I2S_DIN: J2.7, U1.11 (D10)
HEAD_I2S_LRCLK: J2.14, U1.10 (D9)
HEAD_MOTOR_STBY: J2.4, U1.1 (D0)
HEAD_MUX_RST: J2.13, U1.3 (D2)
HEAD_PACK_SENSE: J2.8, U1.4 (D3)
HEAD_PIEZO: J2.10, U1.2 (D1)
HEAD_PWR_HOLD: J2.11, U1.8 (D7)
HEAD_UART0_TX: J2.6, U1.7 (D6)
HEAD_XIAO_5V: J2.1, J2.16, U1.14 (VBUS)

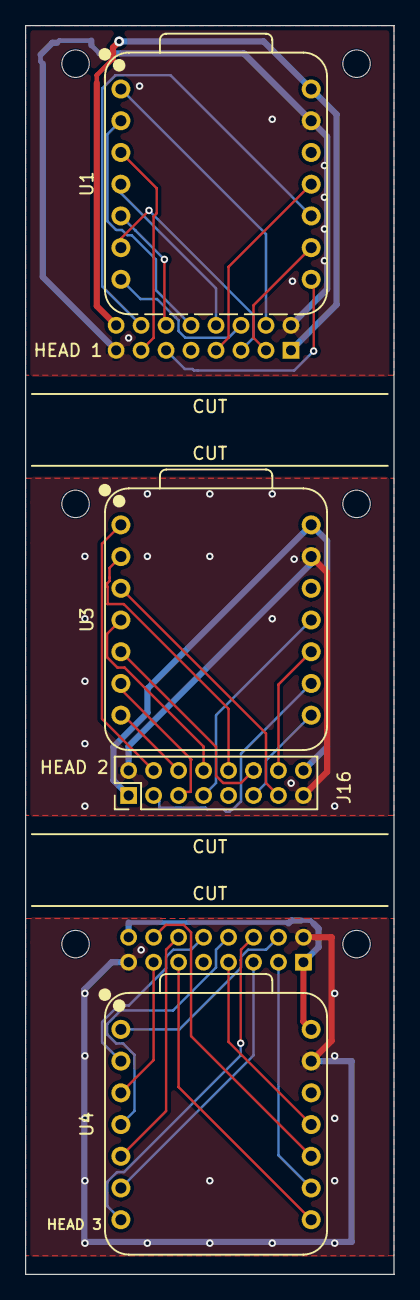
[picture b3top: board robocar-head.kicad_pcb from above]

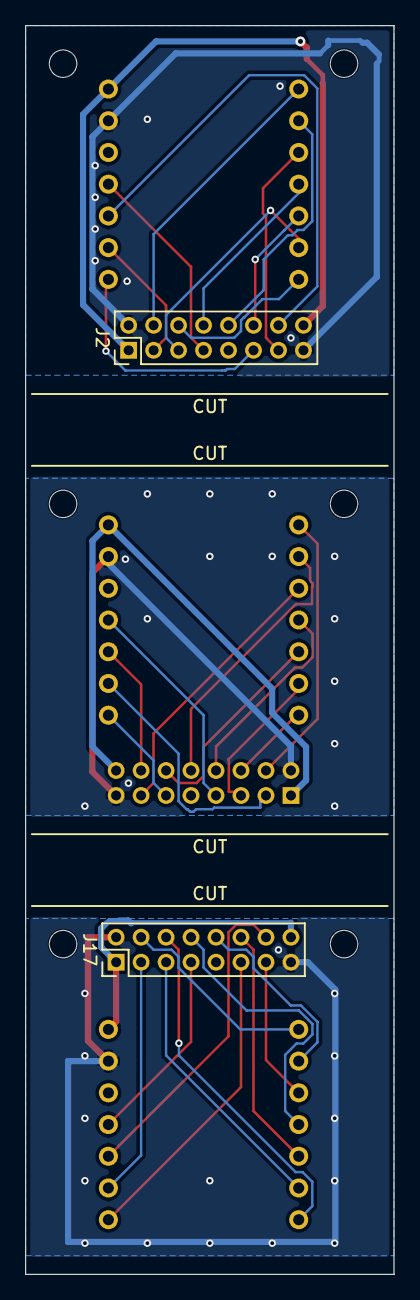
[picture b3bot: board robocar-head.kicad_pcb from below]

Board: 2 copper layers, 29.5 x 100.0 mm, 12 parts (2 on the bottom side), 39 nets.
